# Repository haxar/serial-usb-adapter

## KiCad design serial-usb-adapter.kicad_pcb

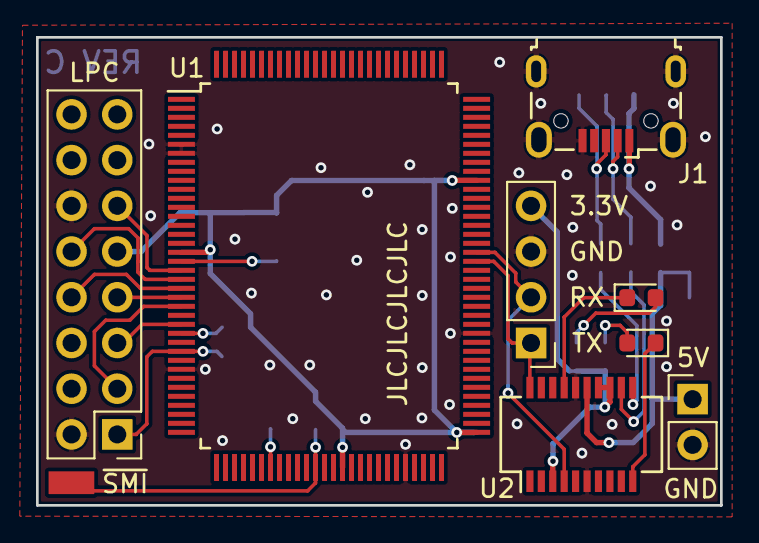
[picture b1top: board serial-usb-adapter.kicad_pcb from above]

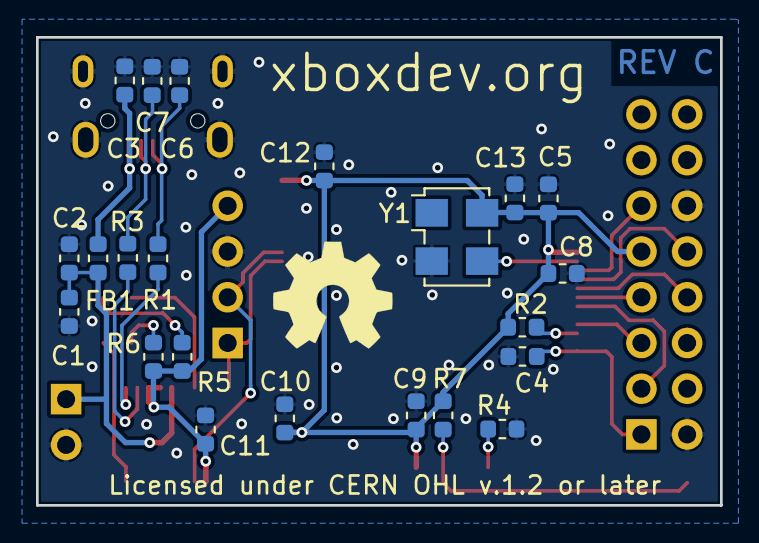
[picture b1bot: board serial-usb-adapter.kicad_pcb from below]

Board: 2 copper layers, 38.0 x 26.0 mm, 31 parts (23 on the bottom side), 26 nets.

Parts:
C1: 4u7; C_0603_1608Metric
C2, C11: 100nF; C_0603_1608Metric
C3, C8, C9, C10, C12, C13: 10nF; C_0603_1608Metric
C4, C6, C7: 47pF; C_0603_1608Metric
C5: 10uF; C_0603_1608Metric
D1: Green; LED_0603_1608Metric
D2: Blue; LED_0603_1608Metric
FB1: 33ohm; L_0603_1608Metric
J1: USB_B_Micro; USB_Micro-B_Wuerth_629105150521
J2: UART Header; PinHeader_1x04_P2.54mm_Vertical
J3: USB Power; PinHeader_1x02_P2.54mm_Vertical
JP1: LPC; PinHeader_2x08_P2.54mm_Vertical
OSHW Logo: OSHW-Symbol_6.7x6mm_SilkScreen
R1, R3: 27R; R_0603_1608Metric
R2, R4: 10k; R_0603_1608Metric
R5: 470R; R_0603_1608Metric
R6: 1.2k; R_0603_1608Metric
R7: 1k; R_0603_1608Metric
U1: LPC47M192; LQFP-128_14x20mm_P0.5mm
U2: FT231XS; SSOP-20_3.9x8.7mm_P0.635mm
Y1: SG5032CAN 14.318MHz; Oscillator_SMD_TXC_7C-4Pin_5.0x3.2mm_HandSoldering

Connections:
+3V3: C11.1, J2.4, R5.1, R6.1, U2.3 (VCCIO), U2.13 (3V3OUT), U2.14 (~RESET)
unnamed: C3.1, FB1.1, J1.1 (VBUS)
unnamed: C4.1, JP1.1 (LCLK), U1.29 (PCI_CLK)
unnamed: C6.1, J1.3 (D+), R1.2
unnamed: C7.1, J1.2 (D-), R3.1
unnamed: D1.1 (K), U2.10 (TXLED#)
unnamed: D1.2 (A), R6.2
unnamed: D2.1 (K), U2.17 (RXLED#)
unnamed: D2.2 (A), R5.2
unnamed: J2.1, U1.84 (RXD1), U2.20 (TXD)
unnamed: J2.2, U1.85 (TXD1), U2.4 (RXD)
unnamed: JP1.3 (LFRAME), U1.24 (nLFRAME)
unnamed: JP1.5 (RST), U1.26 (nPCI_RESET)
unnamed: JP1.7 (LAD3), U1.23 (LAD3)
unnamed: JP1.8 (LAD2), U1.22 (LAD2)
unnamed: JP1.10 (LAD1), U1.21 (LAD1)
unnamed: JP1.11 (LAD0), U1.20 (LAD0)
unnamed: R1.1, U2.11 (USBDP)
unnamed: R2.1, U1.27 (nLPCPD)
unnamed: R3.2, U2.12 (USBDM)
unnamed: R4.1, U1.45 (SYSOPT)
unnamed: U1.19 (CLOCKI), Y1.3 (OUT)
SMI: R7.1, U1.50
VBUS: C1.1, C2.1, FB1.2, J3.1, U2.15 (VCC)
VCC: C5.2, C8.1, C9.1, C10.1, C12.1, C13.2, JP1.9 (VCC), R2.2, R7.2, U1.18 (VTR), U1.53 (VCC), U1.65 (VCC), U1.93 (VCC), Y1.4 (VCC)
VSS: C1.2, C2.2, C3.2, C4.2, C5.1, C6.2, C7.2, C8.2, C9.2, C10.2, C11.2, C12.2, C13.1, J1.5 (GND), J1.6 (Shield), J2.3, J3.2, JP1.2 (VSS), JP1.12, R4.2, U1.6 (CLKI32), U1.7 (VSS), U1.31 (VSS), U1.60 (VSS), U1.76 (VSS), U2.6 (GND), U2.16 (GND), Y1.2 (GND)

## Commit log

2022-04-25 Break out SMI output pin & set thermal spoke width to 0.3 mm for power pads
2022-05-05 Set copper edge clearance to 0.2 mm

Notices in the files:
serial-usb-adapter.kicad_pcb:
Copyright Mike Davis 2019
Licensed under CERN OHL v.1.2 or later
